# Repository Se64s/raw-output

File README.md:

# raw-output

Output stage for eurorack devices.

This module has been inspired by befaco [output](https://www.befaco.org/out-v3/) module, adapted to 3.5mm stereo jacks.

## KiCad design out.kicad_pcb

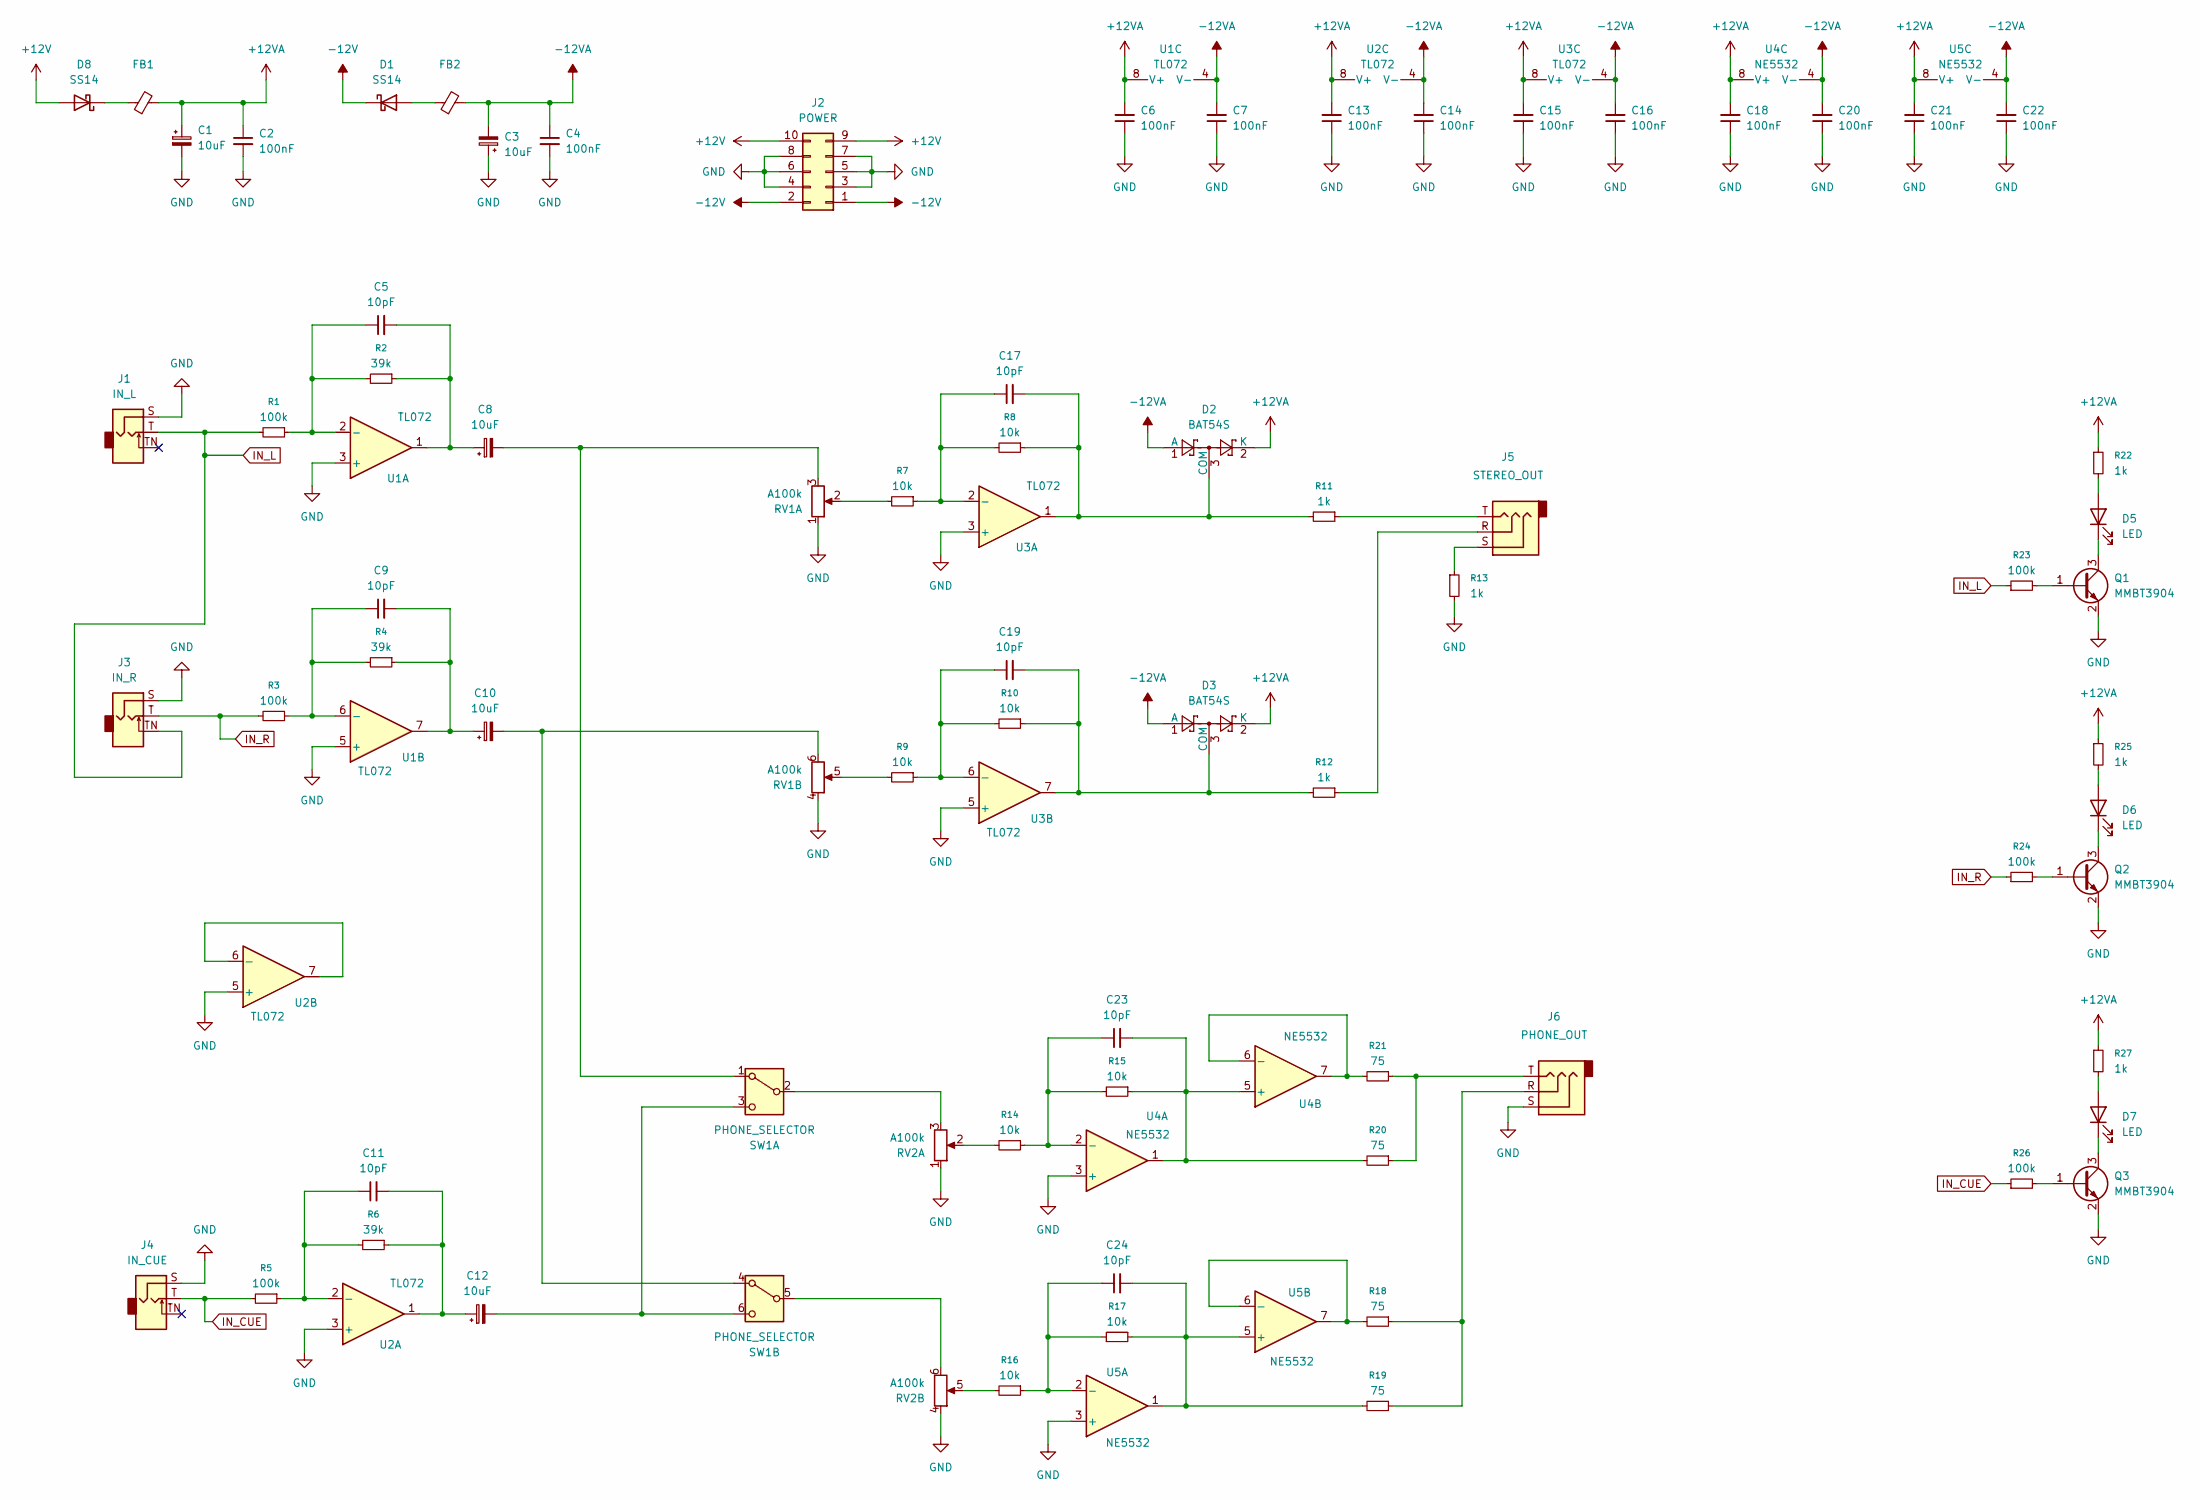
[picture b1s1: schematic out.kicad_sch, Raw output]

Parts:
C1, C3, C8, C10, C12: 10uF; CP_Elec_4x5.4
C2, C4: 100nF; C_0805_2012Metric_Pad1.18x1.45mm_HandSolder
C5, C9, C11, C17, C19, C23, C24: 10pF; C_0603_1608Metric_Pad1.08x0.95mm_HandSolder
C6, C7, C13, C14, C15, C16, C18, C20, C21, C22: 100nF; C_0603_1608Metric_Pad1.08x0.95mm_HandSolder
D1, D8: SS14; D_SMA_Handsoldering
D2, D3: BAT54S; SOT-23
D5, D6, D7: LED; LED_0805_2012Metric_Pad1.15x1.40mm_HandSolder
FB1, FB2: FerriteBead_Small; L_0805_2012Metric_Pad1.05x1.20mm_HandSolder
J1: IN_L; Jack_3.5mm_QingPu_WQP-PJ398SM_Vertical_CircularHoles
J2: POWER; IDC-Header_2x05_P2.54mm_Vertical_SMD
J3: IN_R; Jack_3.5mm_QingPu_WQP-PJ398SM_Vertical_CircularHoles
J4: IN_CUE; Jack_3.5mm_QingPu_WQP-PJ398SM_Vertical_CircularHoles
J5: STEREO_OUT; Jack_3.5mm_TRS_Vertical_CircularHoles
J6: PHONE_OUT; Jack_3.5mm_TRS_Vertical_CircularHoles
Q1, Q2, Q3: MMBT3904; SOT-23
R1, R3, R5, R23, R24, R26: 100k; R_0603_1608Metric_Pad0.98x0.95mm_HandSolder
R2, R4, R6: 39k; R_0603_1608Metric_Pad0.98x0.95mm_HandSolder
R7, R8, R9, R10, R14, R15, R16, R17: 10k; R_0603_1608Metric_Pad0.98x0.95mm_HandSolder
R11, R12, R13, R22, R25, R27: 1k; R_0603_1608Metric_Pad0.98x0.95mm_HandSolder
R18, R19, R20, R21: 75; R_0805_2012Metric_Pad1.20x1.40mm_HandSolder
RV1, RV2: A100k; Potentiometer_Alpha_RD902F-40-00D_Dual_Vertical_CircularHol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
SW1: PHONE_SELECTOR; DWB3_DPDT_SWITCH
U1, U2, U3: TL072; SOIC-8_5.3x6.2mm_P1.27mm
U4, U5: NE5532; SOIC-8_5.3x6.2mm_P1.27mm

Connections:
+12V: D8.2 (A), J2.9, J2.10
+12VA: C1.1, C2.1, C6.2, C13.2, C15.2, C18.2, C21.2, D2.2 (K), D3.2 (K), FB1.2, R22.1, R25.1, R27.1, U1.8 (V+), U2.8 (V+), U3.8 (V+), U4.8 (V+), U5.8 (V+)
-12V: D1.1 (K), J2.1, J2.2
-12VA: C3.2, C4.1, C7.2, C14.2, C16.2, C20.2, C22.2, D2.1 (A), D3.1 (A), FB2.2, U1.4 (V-), U2.4 (V-), U3.4 (V-), U4.4 (V-), U5.4 (V-)
GND: C1.2, C2.2, C3.1, C4.2, C6.1, C7.1, C13.1, C14.1, C15.1, C16.1, C18.1, C20.1, C21.1, C22.1, J1.S, J2.3, J2.4, J2.5, J2.6, J2.7, J2.8, J3.S, J4.S, J6.S, Q1.2 (E), Q2.2 (E), Q3.2 (E), R13.2, RV1.1, RV1.4, RV2.1, RV2.4, U1.3 (+), U1.5 (+), U2.3 (+), U2.5 (+), U3.3 (+), U3.5 (+), U4.3 (+), U5.3 (+)
IN_CUE: J4.T, R5.2, R26.1
IN_L: J1.T, J3.TN, R1.2, R23.1
IN_R: J3.T, R3.2, R24.1
unnamed: C5.2, C8.1, R2.1, U1.1
unnamed: C9.2, C10.1, R4.1, U1.7
unnamed: C11.2, C12.1, R6.1, U2.1
unnamed: D1.2 (A), FB2.1
unnamed: C17.2, D2.3 (COM), R8.1, R11.2, U3.1
unnamed: C19.2, D3.3 (COM), R10.1, R12.2, U3.7
unnamed: D5.2 (A), R22.2
unnamed: D5.1 (K), Q1.3 (C)
unnamed: D6.2 (A), R25.2
unnamed: D6.1 (K), Q2.3 (C)
unnamed: D7.2 (A), R27.2
unnamed: D7.1 (K), Q3.3 (C)
unnamed: D8.1 (K), FB1.1
unnamed: J5.R, R12.1
unnamed: J5.S, R13.1
unnamed: J5.T, R11.1
unnamed: J6.R, R18.1, R19.1
unnamed: J6.T, R20.1, R21.1
unnamed: Q1.1 (B), R23.2
unnamed: Q2.1 (B), R24.2
unnamed: Q3.1 (B), R26.2
unnamed: R7.2, RV1.2
unnamed: R9.2, RV1.5
unnamed: R14.2, RV2.2
unnamed: R16.2, RV2.5
unnamed: C8.2, RV1.3, SW1.1 (A)
unnamed: RV2.3, SW1.2 (B)
unnamed: C12.2, SW1.3 (C), SW1.6 (C)
unnamed: C10.2, RV1.6, SW1.4 (A)
unnamed: RV2.6, SW1.5 (B)
unnamed: C5.1, R1.1, R2.2, U1.2 (-)
unnamed: C9.1, R3.1, R4.2, U1.6 (-)
unnamed: C11.1, R5.1, R6.2, U2.2 (-)
unnamed: U2.6 (-), U2.7
unnamed: C17.1, R7.1, R8.2, U3.2 (-)
unnamed: C19.1, R9.1, R10.2, U3.6 (-)
unnamed: C23.1, R14.1, R15.2, U4.2 (-)
unnamed: C23.2, R15.1, R20.2, U4.1, U4.5 (+)
unnamed: R21.2, U4.6 (-), U4.7
unnamed: C24.1, R16.1, R17.2, U5.2 (-)
unnamed: C24.2, R17.1, R19.2, U5.1, U5.5 (+)
unnamed: R18.2, U5.6 (-), U5.7

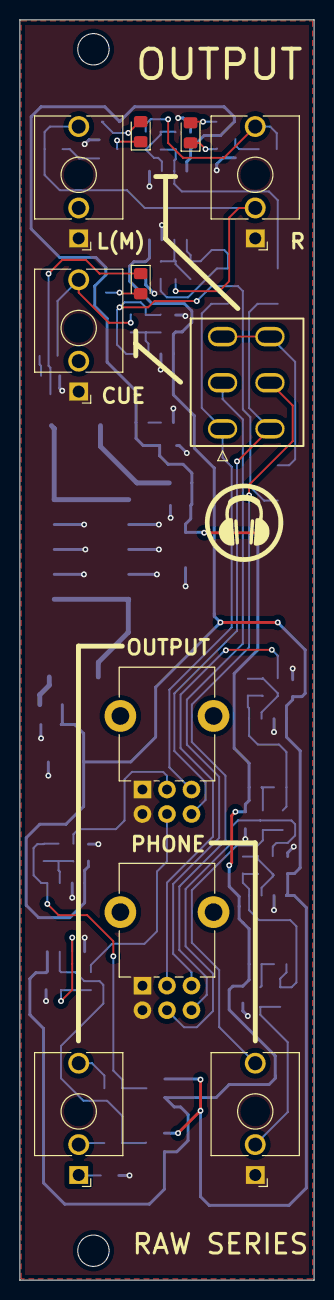
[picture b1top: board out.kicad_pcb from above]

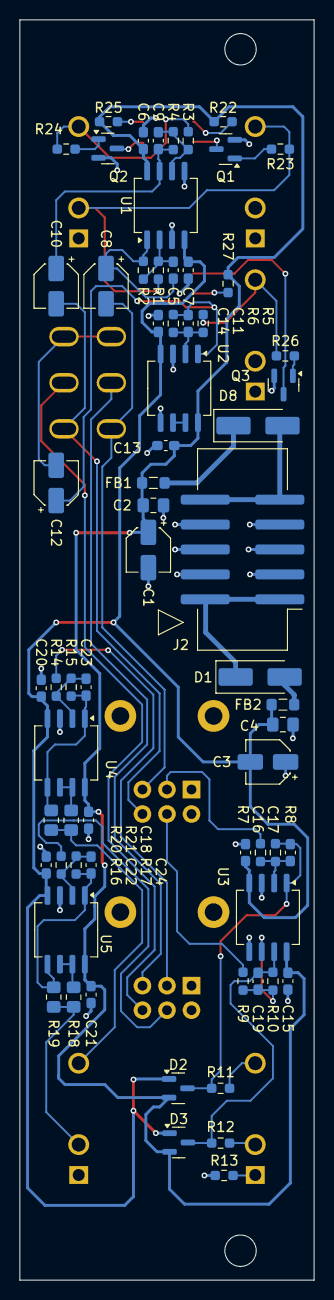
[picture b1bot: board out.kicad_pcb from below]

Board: 4 copper layers, 30.0 x 128.5 mm, 77 parts (66 on the bottom side), 50 nets.

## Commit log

2025-08-31 feat: first commit with sch
2025-08-31 feat: route power planes
2025-09-02 pcb: signal tracks
2025-09-03 wip: routing
2025-09-03 wip: layout
2025-09-03 fix: increase width of input voltage lines
2025-09-03 feat: last touch before fab
2025-09-18 doc: add errors found in first build
2025-09-18 fix: correct errors found in release 1.0.0
2025-09-23 git: remove bom output folder
2025-09-23 doc: add some information about module inspiration
2025-09-23 feat: adapt pcb to two layers, fix opamp and jack routing
